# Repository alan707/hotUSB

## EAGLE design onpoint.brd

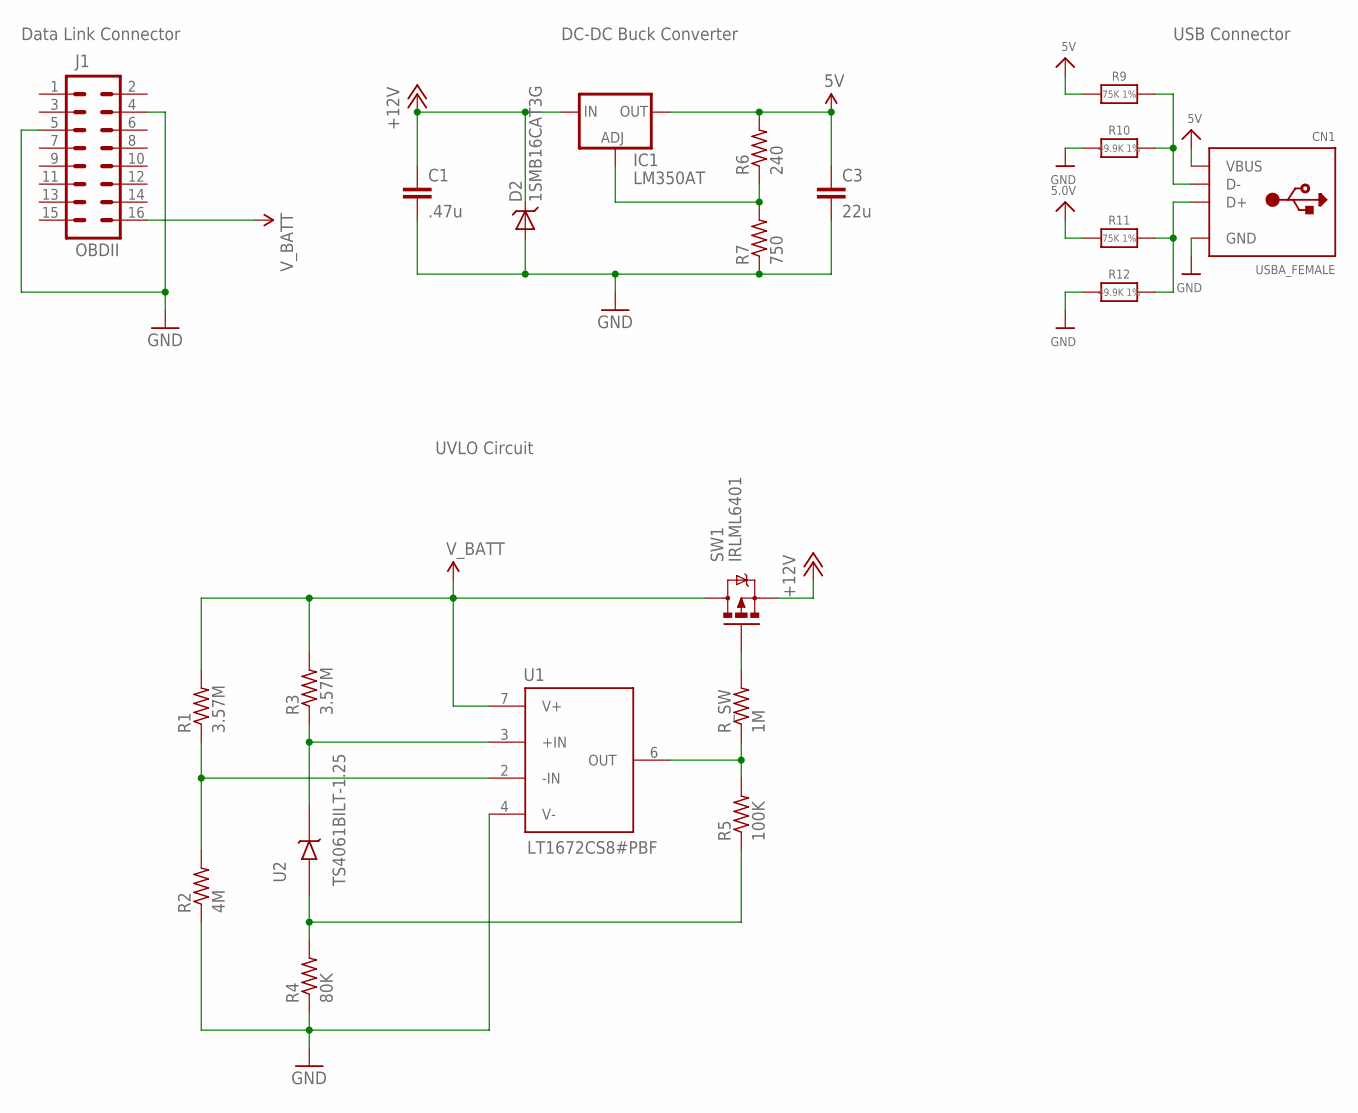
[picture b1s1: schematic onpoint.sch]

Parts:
C1: .47u; C0805; PARTNO C0805C474K5RACTU
C3: 22u; C0805; PARTNO GRM219R61A226MEA0D
CN1: USBA_FEMALE; USB_HOST-PTH
D2: 1SMB16CAT3G; SMB-DIODE; PARTNO 1SMB16CAT3G
IC1: LM350AT; SOT223
J1: OBDII; OBDII-STRAIGHT; PARTNO OBD-II
R1, R3: 3.57M; R0805
R2: 4M; R0805
R4: 80K; R0805
R5: 100K; R0805
R6: 240; R0805
R7: 750; R0805
R9, R11: 75K 1%; 0805-NO
R10, R12: 49.9K 1%; 0805-NO
R_SW: 1M; R0805
SW1: IRLML6401; SOT23-3
U1: LT1672CS8#PBF; MSOP8
U2: TS4061BILT-1.25; SOT23-3L

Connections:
5V: C3.1, CN1.VBUS, IC1.3 (OUT), R6.2, R9.2, R11.2
+12V: C1.1, D2.C, IC1.1 (IN), SW1.2 (S)
D+: CN1.D+, R11.1, R12.1
D-: CN1.D-, R9.1, R10.1
GND: C1.2, C3.2, CN1.GND, D2.A, J1.4, J1.5, R2.1, R4.1, R7.1, R10.2, R12.2, U1.4 (V-)
unnamed: IC1.2 (GND), R6.1, R7.2
unnamed: R5.2, R_SW.1, U1.6 (OUT)
unnamed: R3.1, U1.3 (+IN), U2.1 (K)
unnamed: R1.1, R2.2, U1.2 (-IN)
unnamed: R_SW.2, SW1.1 (G)
unnamed: R4.2, R5.1, U2.2 (A)
V_BATT: J1.16, R1.2, R3.2, SW1.3 (D), U1.7 (V+)

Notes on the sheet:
DC-DC Buck Converter
USB Connector
Data Link Connector
UVLO Circuit

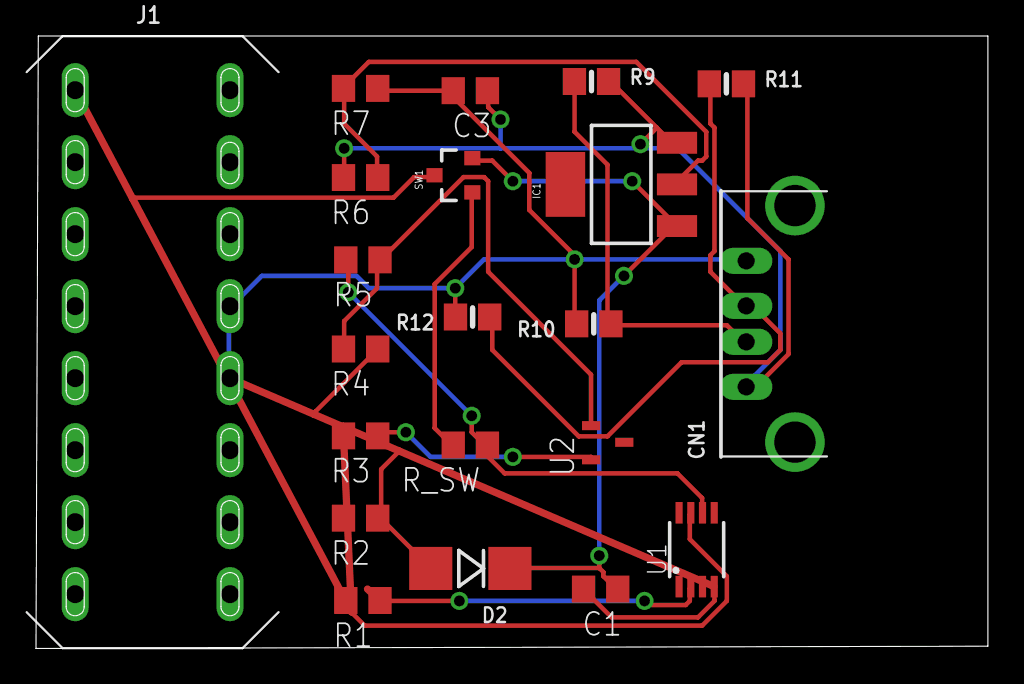
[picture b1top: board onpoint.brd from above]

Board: 2 copper layers, 52.9 x 34.0 mm, 21 parts (0 on the bottom side), 12 nets.

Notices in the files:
parts and their libraries:
microbuilder: This work is placed in the public domain, and may be freely used for commercial and non-commercial work with the following conditions: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
SparkFun-PowerIC: Licensing: Creative Commons ShareAlike 4.0 International - https://creativecommons.org/licenses/by-sa/4.0
